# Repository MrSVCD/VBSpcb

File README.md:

# VBSpcb
A custom PCB for the Video Backup System adapter.
## Versions
### THT - Through-Hole Technology
### SMT - Surface-Mount Technology

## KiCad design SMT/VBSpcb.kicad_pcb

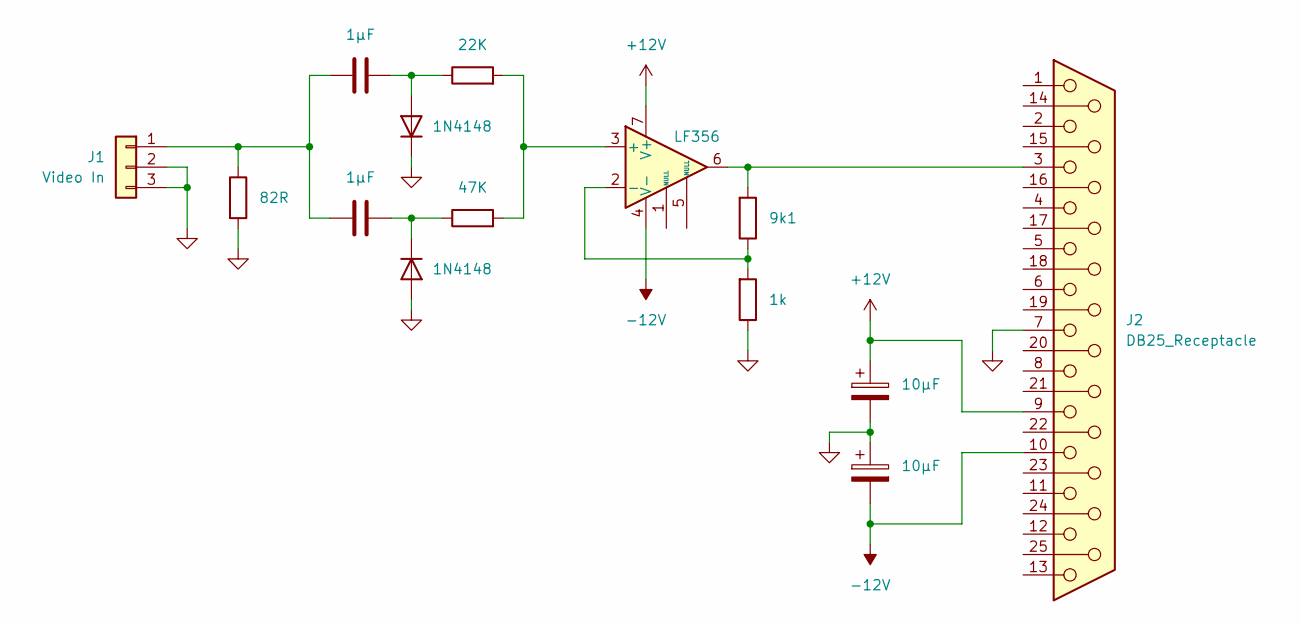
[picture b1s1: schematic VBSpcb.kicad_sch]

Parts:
C1, C2: 1µF; C_1210_3225Metric_Pad1.33x2.70mm_HandSolder
C3, C4: 10µF; CP_Elec_5x5.4
D1, D2: 1N4148; D_SOD-323_HandSoldering
J1: Video In; PinHeader_1x03_P2.54mm_Vertical
J2: DB25_Receptacle; DSUB-25_Female_EdgeMount_P2.77mm
R1: 82R; R_1206_3216Metric_Pad1.30x1.75mm_HandSolder
R2: 22K; R_1206_3216Metric_Pad1.30x1.75mm_HandSolder
R3: 47K; R_1206_3216Metric_Pad1.30x1.75mm_HandSolder
R4: 9k1; R_1206_3216Metric_Pad1.30x1.75mm_HandSolder
R5: 1k; R_1206_3216Metric_Pad1.30x1.75mm_HandSolder
U1: LF356; SO-8_3.9x4.9mm_P1.27mm

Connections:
+12V: C3.1, J2.9, U1.7 (V+)
-12V: C4.2, J2.10, U1.4 (V-)
GND: C3.2, C4.1, D1.1 (K), D2.2 (A), J1.2, J1.3, J2.7, R1.2, R5.1
unnamed: C1.1, D1.2 (A), R2.1
unnamed: C2.2, D2.1 (K), R3.1
unnamed: C1.2, C2.1, J1.1, R1.1
unnamed: J2.3, R4.2, U1.6
unnamed: R2.2, R3.2, U1.3 (+)
unnamed: R4.1, R5.2, U1.2 (-)

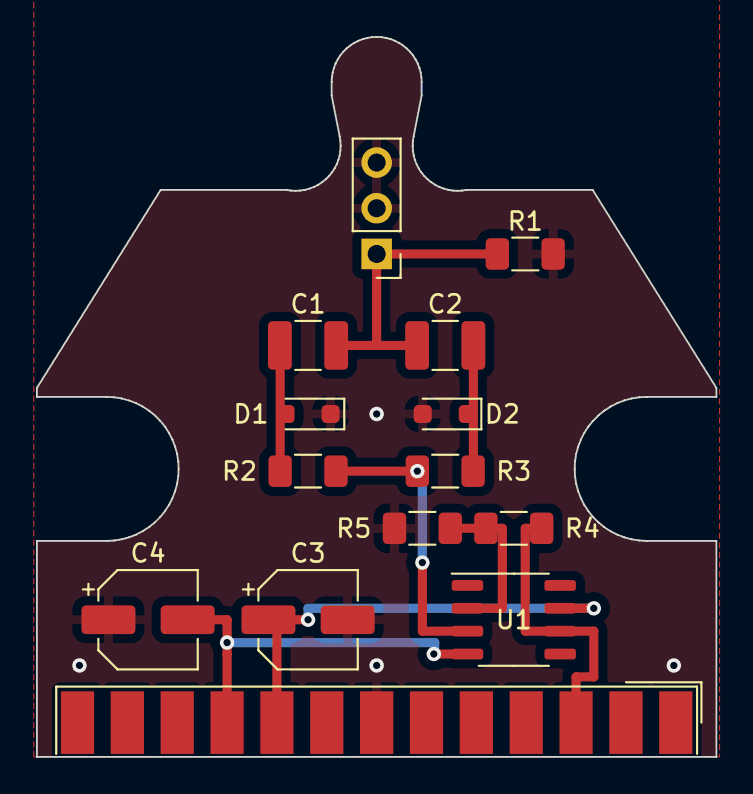
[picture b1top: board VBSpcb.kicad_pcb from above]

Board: 2 copper layers, 37.8 x 40.0 mm, 14 parts (0 on the bottom side), 9 nets.

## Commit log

2023-06-23 Created LICENSE
2023-06-23 Updated Silkscreen
2023-06-23 Added PCB image
2023-06-27 Added nubbin for strain releif
2023-06-27 Updated PCB image
2023-06-28 Added SMT version and moved THT to it's own folder
